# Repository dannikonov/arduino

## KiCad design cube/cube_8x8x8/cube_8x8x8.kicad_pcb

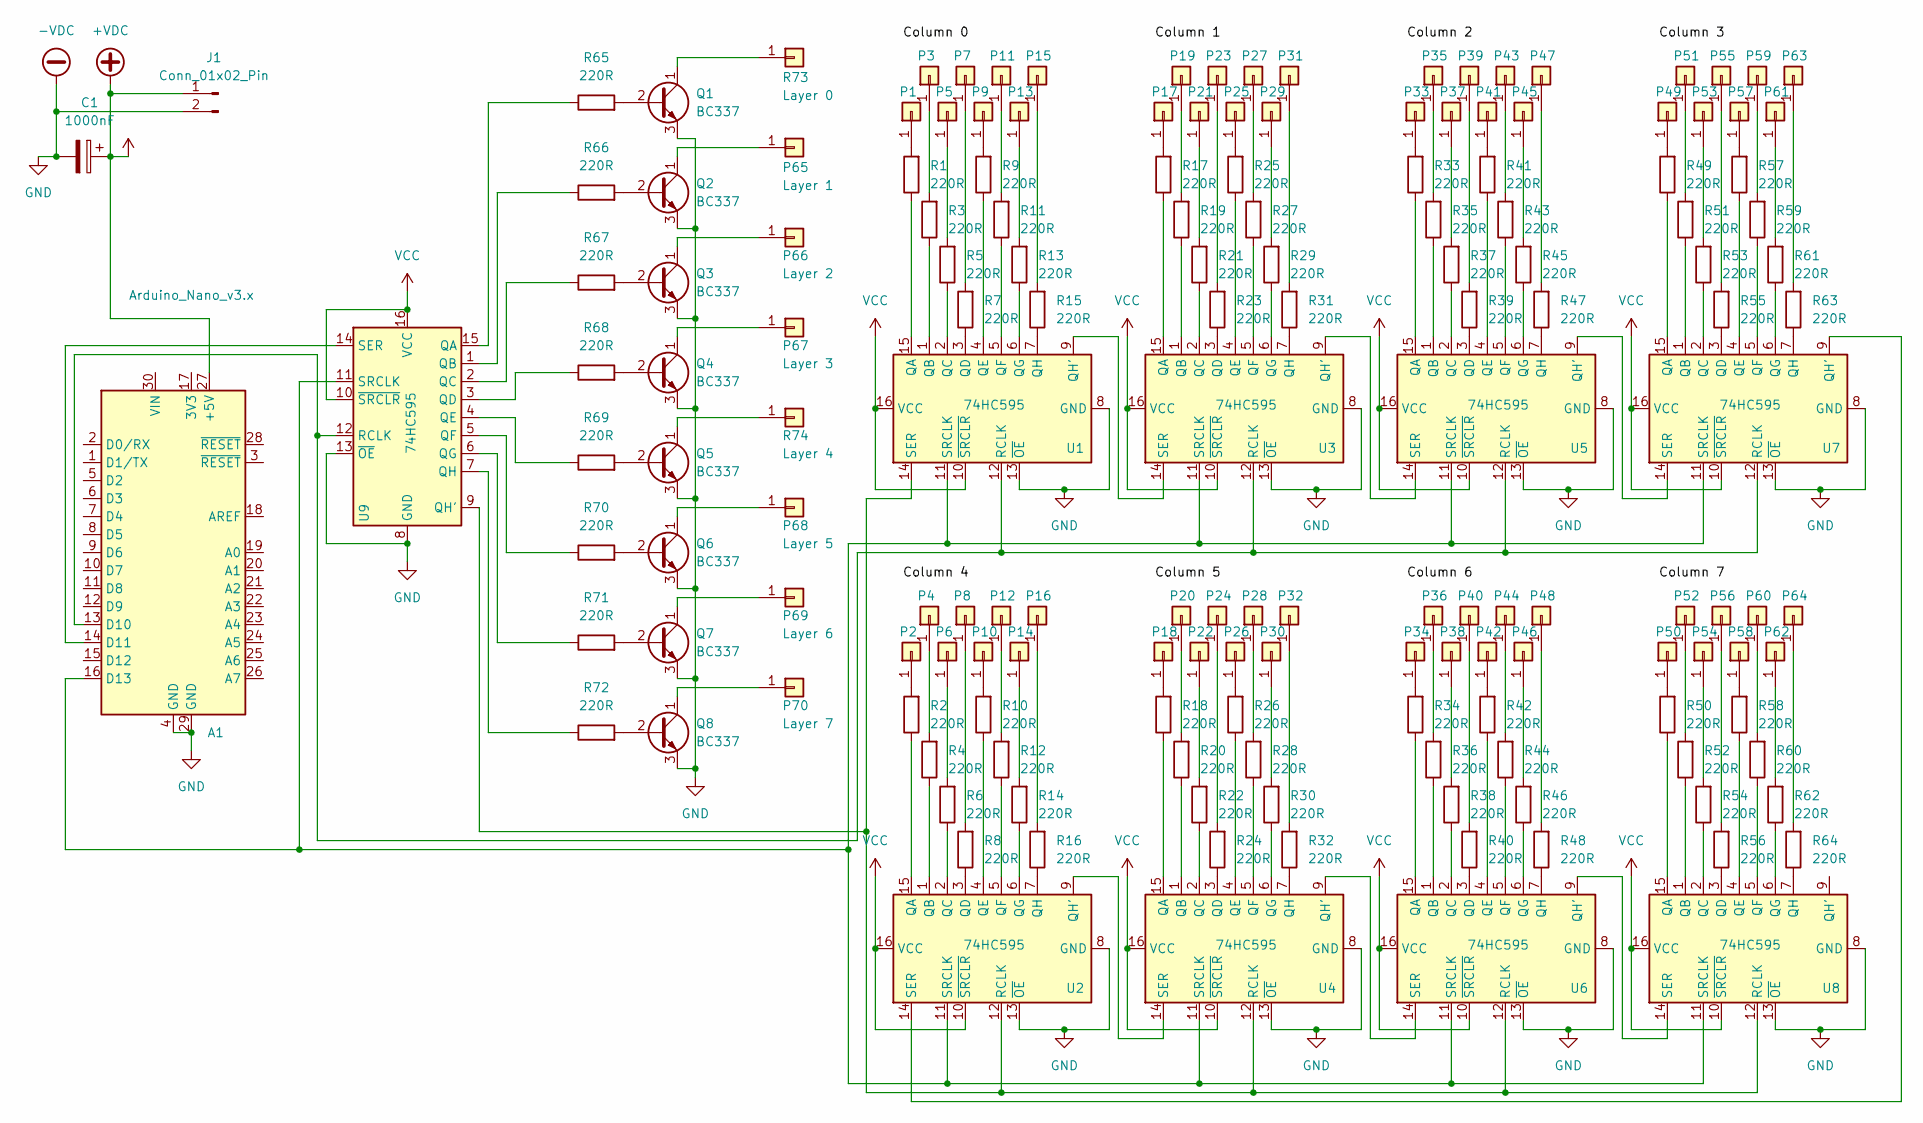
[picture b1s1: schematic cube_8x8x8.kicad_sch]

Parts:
A1: Arduino_Nano_v3.x; Arduino_Nano
C1: 1000nF; CP_Radial_D12.5mm_P5.00mm
J1: Conn_01x02_Pin; PinHeader_1x02_P2.00mm_Vertical
P1: Column_0_0; LED_D5.0mm
P2: Column_4_0; LED_D5.0mm
P3: Column_0_1; LED_D5.0mm
P4: Column_4_1; LED_D5.0mm
P5: Column_0_2; LED_D5.0mm
P6: Column_4_2; LED_D5.0mm
P7: Column_0_3; LED_D5.0mm
P8: Column_4_3; LED_D5.0mm
P9: Column_0_4; LED_D5.0mm
P10: Column_4_4; LED_D5.0mm
P11: Column_0_5; LED_D5.0mm
P12: Column_4_5; LED_D5.0mm
P13: Column_0_6; LED_D5.0mm
P14: Column_4_6; LED_D5.0mm
P15: Column_0_7; LED_D5.0mm
P16: Column_4_7; LED_D5.0mm
P17: Column_1_0; LED_D5.0mm
P18: Column_5_0; LED_D5.0mm
P19: Column_1_1; LED_D5.0mm
P20: Column_5_1; LED_D5.0mm
P21: Column_1_2; LED_D5.0mm
P22: Column_5_2; LED_D5.0mm
P23: Column_1_3; LED_D5.0mm
P24: Column_5_3; LED_D5.0mm
P25: Column_1_4; LED_D5.0mm
P26: Column_5_4; LED_D5.0mm
P27: Column_1_5; LED_D5.0mm
P28: Column_5_5; LED_D5.0mm
P29: Column_1_6; LED_D5.0mm
P30: Column_5_6; LED_D5.0mm
P31: Column_1_7; LED_D5.0mm
P32: Column_5_7; LED_D5.0mm
P33: Column_2_0; LED_D5.0mm
P34: Column_6_0; LED_D5.0mm
P35: Column_2_1; LED_D5.0mm
P36: Column_6_1; LED_D5.0mm
P37: Column_2_2; LED_D5.0mm
P38: Column_6_2; LED_D5.0mm
P39: Column_2_3; LED_D5.0mm
P40: Column_6_3; LED_D5.0mm
P41: Column_2_4; LED_D5.0mm
P42: Column_6_4; LED_D5.0mm
P43: Column_2_5; LED_D5.0mm
P44: Column_6_5; LED_D5.0mm
P45: Column_2_6; LED_D5.0mm
P46: Column_6_6; LED_D5.0mm
P47: Column_2_7; LED_D5.0mm
P48: Column_6_7; LED_D5.0mm
P49: Column_3_0; LED_D5.0mm
P50: Column_7_0; LED_D5.0mm
P51: Column_3_1; LED_D5.0mm
P52: Column_7_1; LED_D5.0mm
P53: Column_3_2; LED_D5.0mm
P54: Column_7_2; LED_D5.0mm
P55: Column_3_3; LED_D5.0mm
P56: Column_7_3; LED_D5.0mm
P57: Column_3_4; LED_D5.0mm
P58: Column_7_4; LED_D5.0mm
P59: Column_3_5; LED_D5.0mm
P60: Column_7_5; LED_D5.0mm
P61: Column_3_6; LED_D5.0mm
P62: Column_7_6; LED_D5.0mm
P63: Column_3_7; LED_D5.0mm
P64: Column_7_7; LED_D5.0mm
P65: Layer 1; SolderWire-0.1sqmm_1x01_D0.4mm_OD1mm
P66: Layer 2; SolderWire-0.1sqmm_1x01_D0.4mm_OD1mm
P67: Layer 3; SolderWire-0.1sqmm_1x01_D0.4mm_OD1mm
P68: Layer 5; SolderWire-0.1sqmm_1x01_D0.4mm_OD1mm
P69: Layer 6; SolderWire-0.1sqmm_1x01_D0.4mm_OD1mm
P70: Layer 7; SolderWire-0.1sqmm_1x01_D0.4mm_OD1mm
Q1, Q2, Q3, Q4, Q5, Q6, Q7, Q8: BC337; TO-92_Inline
R1, R2, R3, R4, R5, R6, R7, R8, R9, R10, R11, R12, R13, R14, R15, R16, R17, R18, R19, R20, R21, R22, R23, R24, R25, R26, R27, R28, R29, R30, R31, R32, R33, R34, R35, R36, R37, R38, R39, R40, R41, R42, R43, R44, R45, R46, R47, R48, R49, R50, R51, R52, R53, R54, R55, R56, R57, R58, R59, R60, R61, R62, R63, R64, R65, R66, R67, R68, R69, R70, R71, R72: 220R; R_Axial_DIN0207_L6.3mm_D2.5mm_P10.16mm_Horizontal
R73: Layer 0; SolderWire-0.1sqmm_1x01_D0.4mm_OD1mm
R74: Layer 4; SolderWire-0.1sqmm_1x01_D0.4mm_OD1mm
U1, U2, U3, U4, U5, U6, U7, U8, U9: 74HC595; DIP-16_W7.62mm

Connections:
+VDC: A1.27 (+5V), C1.1, J1.1, U1.10 (~SRCLR), U1.16 (VCC), U2.10 (~SRCLR), U2.16 (VCC), U3.10 (~SRCLR), U3.16 (VCC), U4.10 (~SRCLR), U4.16 (VCC), U5.10 (~SRCLR), U5.16 (VCC), U6.10 (~SRCLR), U6.16 (VCC), U7.10 (~SRCLR), U7.16 (VCC), U8.10 (~SRCLR), U8.16 (VCC), U9.10 (~SRCLR), U9.16 (VCC)
-VDC: A1.4 (GND), A1.29 (GND), C1.2, J1.2, Q1.3 (E), Q2.3 (E), Q3.3 (E), Q4.3 (E), Q5.3 (E), Q6.3 (E), Q7.3 (E), Q8.3 (E), U1.8 (GND), U1.13 (~OE), U2.8 (GND), U2.13 (~OE), U3.8 (GND), U3.13 (~OE), U4.8 (GND), U4.13 (~OE), U5.8 (GND), U5.13 (~OE), U6.8 (GND), U6.13 (~OE), U7.8 (GND), U7.13 (~OE), U8.8 (GND), U8.13 (~OE), U9.8 (GND), U9.13 (~OE)
unnamed: A1.13 (D10), U1.12 (RCLK), U3.12 (RCLK), U5.12 (RCLK), U7.12 (RCLK), U9.12 (RCLK)
unnamed: A1.14 (D11), U9.14 (SER)
unnamed: A1.16 (D13), U1.11 (SRCLK), U2.11 (SRCLK), U3.11 (SRCLK), U4.11 (SRCLK), U5.11 (SRCLK), U6.11 (SRCLK), U7.11 (SRCLK), U8.11 (SRCLK), U9.11 (SRCLK)
unnamed: P1.1, R1.2
unnamed: P2.1, R2.2
unnamed: P3.1, R3.2
unnamed: P4.1, R4.2
unnamed: P5.1, R5.2
unnamed: P6.1, R6.2
unnamed: P7.1, R7.2
unnamed: P8.1, R8.2
unnamed: P9.1, R9.2
unnamed: P10.1, R10.2
unnamed: P11.1, R11.2
unnamed: P12.1, R12.2
unnamed: P13.1, R13.2
unnamed: P14.1, R14.2
unnamed: P15.1, R15.2
unnamed: P16.1, R16.2
unnamed: P17.1, R17.2
unnamed: P18.1, R18.2
unnamed: P19.1, R19.2
unnamed: P20.1, R20.2
unnamed: P21.1, R21.2
unnamed: P22.1, R22.2
unnamed: P23.1, R23.2
unnamed: P24.1, R24.2
unnamed: P25.1, R25.2
unnamed: P26.1, R26.2
unnamed: P27.1, R27.2
unnamed: P28.1, R28.2
unnamed: P29.1, R29.2
unnamed: P30.1, R30.2
unnamed: P31.1, R31.2
unnamed: P32.1, R32.2
unnamed: P33.1, R33.2
unnamed: P34.1, R34.2
unnamed: P35.1, R35.2
unnamed: P36.1, R36.2
unnamed: P37.1, R37.2
unnamed: P38.1, R38.2
unnamed: P39.1, R39.2
unnamed: P40.1, R40.2
unnamed: P41.1, R41.2
unnamed: P42.1, R42.2
unnamed: P43.1, R43.2
unnamed: P44.1, R44.2
unnamed: P45.1, R45.2
unnamed: P46.1, R46.2
unnamed: P47.1, R47.2
unnamed: P48.1, R48.2
unnamed: P49.1, R49.2
unnamed: P50.1, R50.2
unnamed: P51.1, R51.2
unnamed: P52.1, R52.2
unnamed: P53.1, R53.2
unnamed: P54.1, R54.2
unnamed: P55.1, R55.2
unnamed: P56.1, R56.2
unnamed: P57.1, R57.2
unnamed: P58.1, R58.2
unnamed: P59.1, R59.2
unnamed: P60.1, R60.2
unnamed: P61.1, R61.2
unnamed: P62.1, R62.2
unnamed: P63.1, R63.2
unnamed: P64.1, R64.2
unnamed: P65.1, Q2.1 (C)
unnamed: P66.1, Q3.1 (C)
unnamed: P67.1, Q4.1 (C)
unnamed: P68.1, Q6.1 (C)
unnamed: P69.1, Q7.1 (C)
unnamed: P70.1, Q8.1 (C)
unnamed: Q1.2 (B), R65.2
unnamed: Q1.1 (C), R73.1
unnamed: Q2.2 (B), R66.2
unnamed: Q3.2 (B), R67.2
unnamed: Q4.2 (B), R68.2
unnamed: Q5.2 (B), R69.2
unnamed: Q5.1 (C), R74.1
unnamed: Q6.2 (B), R70.2
unnamed: Q7.2 (B), R71.2
unnamed: Q8.2 (B), R72.2
unnamed: R1.1, U1.15 (QA)
unnamed: R3.1, U1.1 (QB)
unnamed: R5.1, U1.2 (QC)
unnamed: R7.1, U1.3 (QD)
unnamed: R9.1, U1.4 (QE)
unnamed: R11.1, U1.5 (QF)
unnamed: R13.1, U1.6 (QG)
unnamed: U1.9 (QH'), U3.14 (SER)
unnamed: R15.1, U1.7 (QH)
unnamed: U1.14 (SER), U2.12 (RCLK), U4.12 (RCLK), U6.12 (RCLK), U8.12 (RCLK), U9.9 (QH')
unnamed: R2.1, U2.15 (QA)
unnamed: R4.1, U2.1 (QB)
unnamed: R6.1, U2.2 (QC)
unnamed: R8.1, U2.3 (QD)
unnamed: R10.1, U2.4 (QE)
unnamed: R12.1, U2.5 (QF)
unnamed: R14.1, U2.6 (QG)
unnamed: U2.9 (QH'), U4.14 (SER)
unnamed: R16.1, U2.7 (QH)
unnamed: U2.14 (SER), U7.9 (QH')
unnamed: R17.1, U3.15 (QA)
unnamed: R19.1, U3.1 (QB)
unnamed: R21.1, U3.2 (QC)
unnamed: R23.1, U3.3 (QD)
unnamed: R25.1, U3.4 (QE)
unnamed: R27.1, U3.5 (QF)
unnamed: R29.1, U3.6 (QG)
unnamed: U3.9 (QH'), U5.14 (SER)
unnamed: R31.1, U3.7 (QH)
unnamed: R18.1, U4.15 (QA)
unnamed: R20.1, U4.1 (QB)
unnamed: R22.1, U4.2 (QC)
unnamed: R24.1, U4.3 (QD)
unnamed: R26.1, U4.4 (QE)
unnamed: R28.1, U4.5 (QF)
unnamed: R30.1, U4.6 (QG)
unnamed: U4.9 (QH'), U6.14 (SER)
unnamed: R32.1, U4.7 (QH)
unnamed: R33.1, U5.15 (QA)
unnamed: R35.1, U5.1 (QB)
unnamed: R37.1, U5.2 (QC)
unnamed: R39.1, U5.3 (QD)
unnamed: R41.1, U5.4 (QE)
unnamed: R43.1, U5.5 (QF)
unnamed: R45.1, U5.6 (QG)
unnamed: U5.9 (QH'), U7.14 (SER)
unnamed: R47.1, U5.7 (QH)
unnamed: R34.1, U6.15 (QA)
unnamed: R36.1, U6.1 (QB)
unnamed: R38.1, U6.2 (QC)
unnamed: R40.1, U6.3 (QD)
unnamed: R42.1, U6.4 (QE)
unnamed: R44.1, U6.5 (QF)
unnamed: R46.1, U6.6 (QG)
unnamed: U6.9 (QH'), U8.14 (SER)
unnamed: R48.1, U6.7 (QH)
unnamed: R49.1, U7.15 (QA)
unnamed: R51.1, U7.1 (QB)
unnamed: R53.1, U7.2 (QC)
unnamed: R55.1, U7.3 (QD)
unnamed: R57.1, U7.4 (QE)
unnamed: R59.1, U7.5 (QF)
unnamed: R61.1, U7.6 (QG)
unnamed: R63.1, U7.7 (QH)
unnamed: R50.1, U8.15 (QA)
unnamed: R52.1, U8.1 (QB)
unnamed: R54.1, U8.2 (QC)
unnamed: R56.1, U8.3 (QD)
unnamed: R58.1, U8.4 (QE)
unnamed: R60.1, U8.5 (QF)
unnamed: R62.1, U8.6 (QG)
unnamed: R64.1, U8.7 (QH)
unnamed: R65.1, U9.15 (QA)
unnamed: R66.1, U9.1 (QB)
unnamed: R67.1, U9.2 (QC)
unnamed: R68.1, U9.3 (QD)
unnamed: R69.1, U9.4 (QE)
unnamed: R70.1, U9.5 (QF)
unnamed: R71.1, U9.6 (QG)
unnamed: R72.1, U9.7 (QH)

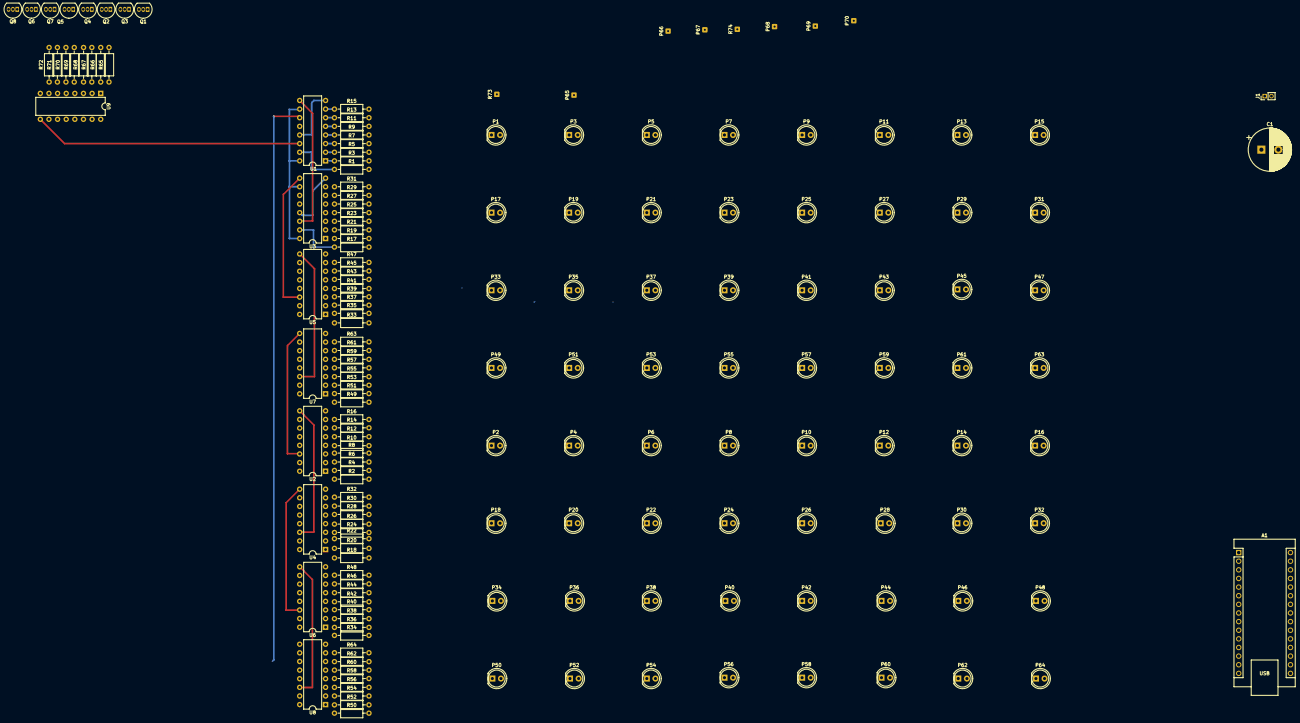
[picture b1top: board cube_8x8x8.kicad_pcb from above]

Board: 2 copper layers, 164 parts (0 on the bottom side), 165 nets.

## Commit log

2024-05-30 led binary counter (8 led)
2024-05-31 ws2812b
2024-06-01 led 4x4x4 cube (1 layer)
2024-06-21 0.96 OLED display and joystic
2024-06-21 add gitignore
2024-06-22 snake started
2024-07-21 support layers in cube
2024-07-28 add ir in ws2812
2024-08-17 cube kicad
2025-03-08 feat: example
2025-03-09 fix: output sensors' data in json
2025-03-11 feat: wrapper example
2025-03-11 fix: rm cached
2025-03-12 fix: disable led
2025-03-12 feat: support prometheus
2025-03-23 feat: esp32
2025-03-23 fix: esp32
2025-03-26 feat: programms
2025-03-27 feat: program channel, fix: program switch
2025-03-29 feat: conf
2025-03-31 feat: i2c scanner
2025-04-05 feat: go wrapper
2025-04-06 fix: docker
2025-05-04 feat: esp32 as receiver, esp8266 sender with sensor
2025-06-01 feat: encoder, tft 7735, main module
2025-06-01 fix: encoder, constants
2025-06-01 feat: encoder
2025-06-06 feat: encoder+tft
2025-06-07 feat: examples
2025-06-08 feat: encoder + led
2025-06-14 fix: encoders
2025-06-14 ref: files
2025-06-14 fix: tft refresh
2025-06-14 fix: i2c pins
2025-06-14 feat: add ssd1306
2025-08-02 feat: functions
2025-08-08 feat: manualColor program
